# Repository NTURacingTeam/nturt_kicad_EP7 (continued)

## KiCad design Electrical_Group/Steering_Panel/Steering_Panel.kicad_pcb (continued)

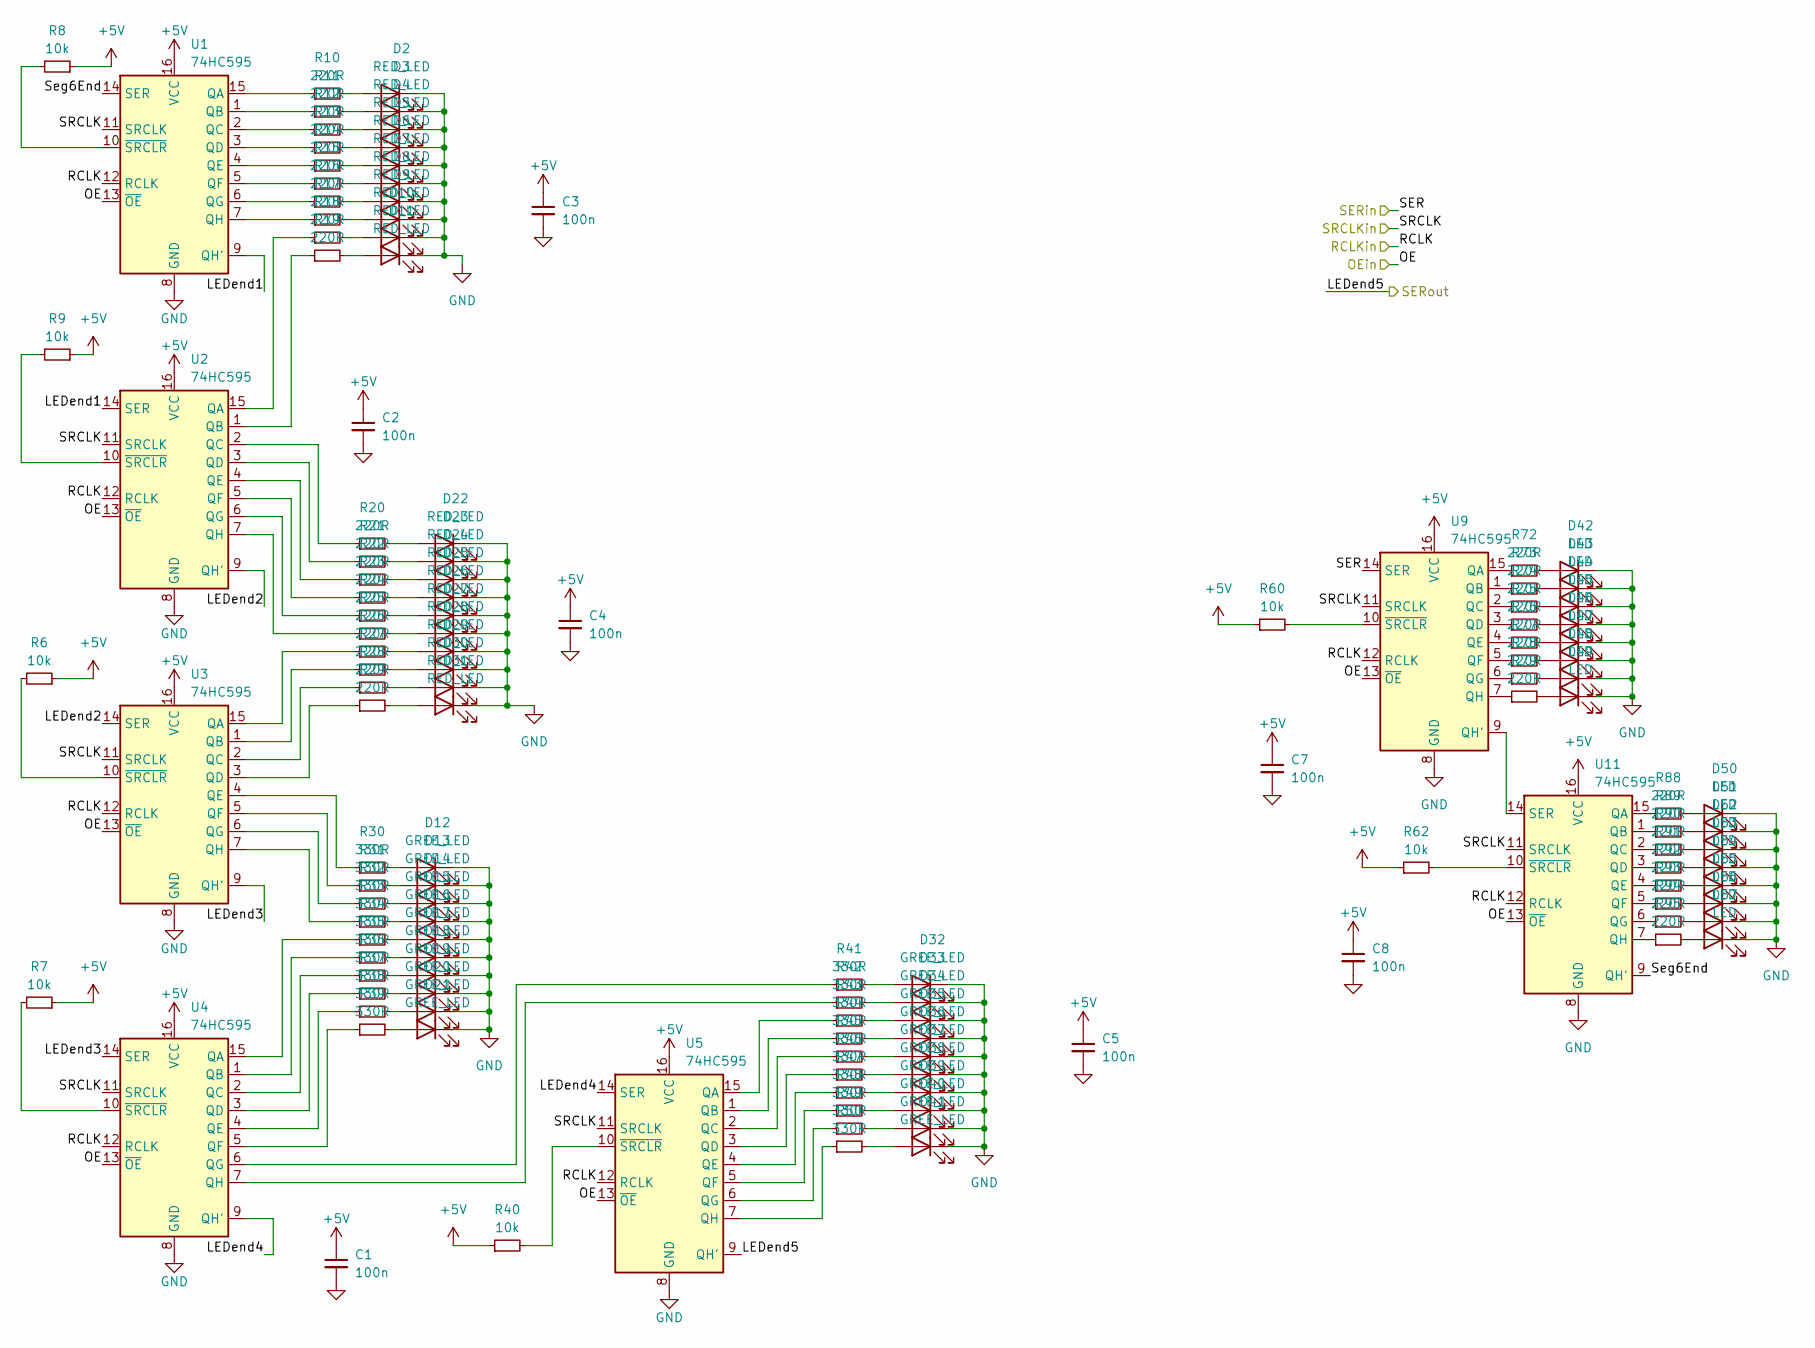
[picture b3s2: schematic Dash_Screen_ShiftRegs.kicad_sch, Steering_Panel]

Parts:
C1, C2, C3, C4, C5, C7, C8: 100n; C_0603_1608Metric
D2, D3, D4, D5, D6, D7, D8, D9, D10, D11, D22, D23, D24, D25, D26, D27, D28, D29, D30, D31: RED_LED; LED_0805_2012Metric_Pad1.15x1.40mm_HandSolder
D12, D13, D14, D15, D16, D17, D18, D19, D20, D21, D32, D33, D34, D35, D36, D37, D38, D39, D40, D41: GREE_LED; LED_0805_2012Metric_Pad1.15x1.40mm_HandSolder
D42, D43, D44, D45, D46, D47, D48, D49, D50, D51, D52, D53, D54, D55, D56, D57: LED; LED_0805_2012Metric_Pad1.15x1.40mm_HandSolder
R6, R7, R8, R9, R40, R60, R62: 10k; R_0603_1608Metric
R10, R11, R12, R13, R14, R15, R16, R17, R18, R19, R20, R21, R22, R23, R24, R25, R26, R27, R28, R29, R72, R73, R74, R75, R76, R77, R78, R79, R88, R89, R90, R91, R92, R93, R94, R95: 220R; R_0603_1608Metric_Pad0.98x0.95mm_HandSolder
R30, R31, R32, R33, R34, R35, R36, R37, R38, R39, R41, R42, R43, R44, R45, R46, R47, R48, R49, R50: 330R; R_0603_1608Metric_Pad0.98x0.95mm_HandSolder
U1, U2, U3, U4, U5, U9, U11: 74HC595; SOIC-16_3.9x9.9mm_P1.27mm

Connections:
+5V: C1.1, C2.1, C3.1, C4.1, C5.1, C7.1, C8.1, R6.1, R7.1, R8.1, R9.1, R40.1, R60.1, R62.1, U1.16 (VCC), U2.16 (VCC), U3.16 (VCC), U4.16 (VCC), U5.16 (VCC), U9.16 (VCC), U11.16 (VCC); also elsewhere on the board
/Dash_Screen_ShiftRegs/LEDend1: U1.9 (QH'), U2.14 (SER)
/Dash_Screen_ShiftRegs/LEDend2: U2.9 (QH'), U3.14 (SER)
/Dash_Screen_ShiftRegs/LEDend3: U3.9 (QH'), U4.14 (SER)
/Dash_Screen_ShiftRegs/LEDend4: U4.9 (QH'), U5.14 (SER)
/Dash_Screen_ShiftRegs/LEDend5: U5.9 (QH'); also elsewhere on the board
/Dash_Screen_ShiftRegs/OE: U1.13 (~OE), U2.13 (~OE), U3.13 (~OE), U4.13 (~OE), U5.13 (~OE), U9.13 (~OE), U11.13 (~OE); also elsewhere on the board
/Dash_Screen_ShiftRegs/RCLK: U1.12 (RCLK), U2.12 (RCLK), U3.12 (RCLK), U4.12 (RCLK), U5.12 (RCLK), U9.12 (RCLK), U11.12 (RCLK); also elsewhere on the board
/Dash_Screen_ShiftRegs/SER: U9.14 (SER); also elsewhere on the board
/Dash_Screen_ShiftRegs/SRCLK: U1.11 (SRCLK), U2.11 (SRCLK), U3.11 (SRCLK), U4.11 (SRCLK), U5.11 (SRCLK), U9.11 (SRCLK), U11.11 (SRCLK); also elsewhere on the board
/Dash_Screen_ShiftRegs/Seg6End: U1.14 (SER), U11.9 (QH')
GND: C1.2, C2.2, C3.2, C4.2, C5.2, C7.2, C8.2, D2.1 (K), D3.1 (K), D4.1 (K), D5.1 (K), D6.1 (K), D7.1 (K), D8.1 (K), D9.1 (K), D10.1 (K), D11.1 (K), D12.1 (K), D13.1 (K), D14.1 (K), D15.1 (K), D16.1 (K), D17.1 (K), D18.1 (K), D19.1 (K), D20.1 (K), D21.1 (K), D22.1 (K), D23.1 (K), D24.1 (K), D25.1 (K), D26.1 (K), D27.1 (K), D28.1 (K), D29.1 (K), D30.1 (K), D31.1 (K), D32.1 (K), D33.1 (K), D34.1 (K), D35.1 (K), D36.1 (K), D37.1 (K), D38.1 (K), D39.1 (K), D40.1 (K), D41.1 (K), D42.1 (K), D43.1 (K), D44.1 (K), D45.1 (K), D46.1 (K), D47.1 (K), D48.1 (K), D49.1 (K), D50.1 (K), D51.1 (K), D52.1 (K), D53.1 (K), D54.1 (K), D55.1 (K), D56.1 (K), D57.1 (K), U1.8 (GND), U2.8 (GND), U3.8 (GND), U4.8 (GND), U5.8 (GND), U9.8 (GND), U11.8 (GND); also elsewhere on the board
unnamed: D2.2 (A), R10.2
unnamed: D3.2 (A), R11.2
unnamed: D4.2 (A), R12.2
unnamed: D5.2 (A), R13.2
unnamed: D6.2 (A), R14.2
unnamed: D7.2 (A), R15.2
unnamed: D8.2 (A), R16.2
unnamed: D9.2 (A), R17.2
unnamed: D10.2 (A), R18.2
unnamed: D11.2 (A), R19.2
unnamed: D12.2 (A), R30.2
unnamed: D13.2 (A), R31.2
unnamed: D14.2 (A), R32.2
unnamed: D15.2 (A), R33.2
unnamed: D16.2 (A), R34.2
unnamed: D17.2 (A), R35.2
unnamed: D18.2 (A), R36.2
unnamed: D19.2 (A), R37.2
unnamed: D20.2 (A), R38.2
unnamed: D21.2 (A), R39.2
unnamed: D22.2 (A), R20.2
unnamed: D23.2 (A), R21.2
unnamed: D24.2 (A), R22.2
unnamed: D25.2 (A), R23.2
unnamed: D26.2 (A), R24.2
unnamed: D27.2 (A), R25.2
unnamed: D28.2 (A), R26.2
unnamed: D29.2 (A), R27.2
unnamed: D30.2 (A), R28.2
unnamed: D31.2 (A), R29.2
unnamed: D32.2 (A), R41.2
unnamed: D33.2 (A), R42.2
unnamed: D34.2 (A), R43.2
unnamed: D35.2 (A), R44.2
unnamed: D36.2 (A), R45.2
unnamed: D37.2 (A), R46.2
unnamed: D38.2 (A), R47.2
unnamed: D39.2 (A), R48.2
unnamed: D40.2 (A), R49.2
unnamed: D41.2 (A), R50.2
unnamed: D42.2 (A), R72.2
unnamed: D43.2 (A), R73.2
unnamed: D44.2 (A), R74.2
unnamed: D45.2 (A), R75.2
unnamed: D46.2 (A), R76.2
unnamed: D47.2 (A), R77.2
unnamed: D48.2 (A), R78.2
unnamed: D49.2 (A), R79.2
unnamed: D50.2 (A), R88.2
unnamed: D51.2 (A), R89.2
unnamed: D52.2 (A), R90.2
unnamed: D53.2 (A), R91.2
unnamed: D54.2 (A), R92.2
unnamed: D55.2 (A), R93.2
unnamed: D56.2 (A), R94.2
unnamed: D57.2 (A), R95.2
unnamed: R10.1, U1.15 (QA)
unnamed: R11.1, U1.1 (QB)
unnamed: R12.1, U1.2 (QC)
unnamed: R13.1, U1.3 (QD)
unnamed: R14.1, U1.4 (QE)
unnamed: R15.1, U1.5 (QF)
unnamed: R16.1, U1.6 (QG)
unnamed: R17.1, U1.7 (QH)
unnamed: R8.2, U1.10 (~SRCLR)
unnamed: R18.1, U2.15 (QA)
unnamed: R19.1, U2.1 (QB)
unnamed: R20.1, U2.2 (QC)
unnamed: R21.1, U2.3 (QD)
unnamed: R22.1, U2.4 (QE)
unnamed: R23.1, U2.5 (QF)
unnamed: R24.1, U2.6 (QG)
unnamed: R25.1, U2.7 (QH)
unnamed: R9.2, U2.10 (~SRCLR)
unnamed: R26.1, U3.15 (QA)
unnamed: R27.1, U3.1 (QB)
unnamed: R28.1, U3.2 (QC)
unnamed: R29.1, U3.3 (QD)
unnamed: R30.1, U3.4 (QE)
unnamed: R31.1, U3.5 (QF)
unnamed: R32.1, U3.6 (QG)
unnamed: R33.1, U3.7 (QH)
unnamed: R6.2, U3.10 (~SRCLR)
unnamed: R34.1, U4.15 (QA)
unnamed: R35.1, U4.1 (QB)
unnamed: R36.1, U4.2 (QC)
unnamed: R37.1, U4.3 (QD)
unnamed: R38.1, U4.4 (QE)
unnamed: R39.1, U4.5 (QF)
unnamed: R41.1, U4.6 (QG)
unnamed: R42.1, U4.7 (QH)
unnamed: R7.2, U4.10 (~SRCLR)
unnamed: R43.1, U5.15 (QA)
unnamed: R44.1, U5.1 (QB)
unnamed: R45.1, U5.2 (QC)
unnamed: R46.1, U5.3 (QD)
unnamed: R47.1, U5.4 (QE)
unnamed: R48.1, U5.5 (QF)
unnamed: R49.1, U5.6 (QG)
unnamed: R50.1, U5.7 (QH)
unnamed: R40.2, U5.10 (~SRCLR)
unnamed: R72.1, U9.15 (QA)
unnamed: R73.1, U9.1 (QB)
unnamed: R74.1, U9.2 (QC)
unnamed: R75.1, U9.3 (QD)
unnamed: R76.1, U9.4 (QE)
unnamed: R77.1, U9.5 (QF)
unnamed: R78.1, U9.6 (QG)
unnamed: R79.1, U9.7 (QH)
unnamed: R60.2, U9.10 (~SRCLR)
unnamed: R88.1, U11.15 (QA)
unnamed: R89.1, U11.1 (QB)
unnamed: R90.1, U11.2 (QC)
unnamed: R91.1, U11.3 (QD)
unnamed: R92.1, U11.4 (QE)
unnamed: R93.1, U11.5 (QF)
unnamed: R94.1, U11.6 (QG)
unnamed: R95.1, U11.7 (QH)
unnamed: U9.9 (QH'), U11.14 (SER)
unnamed: R62.2, U11.10 (~SRCLR)

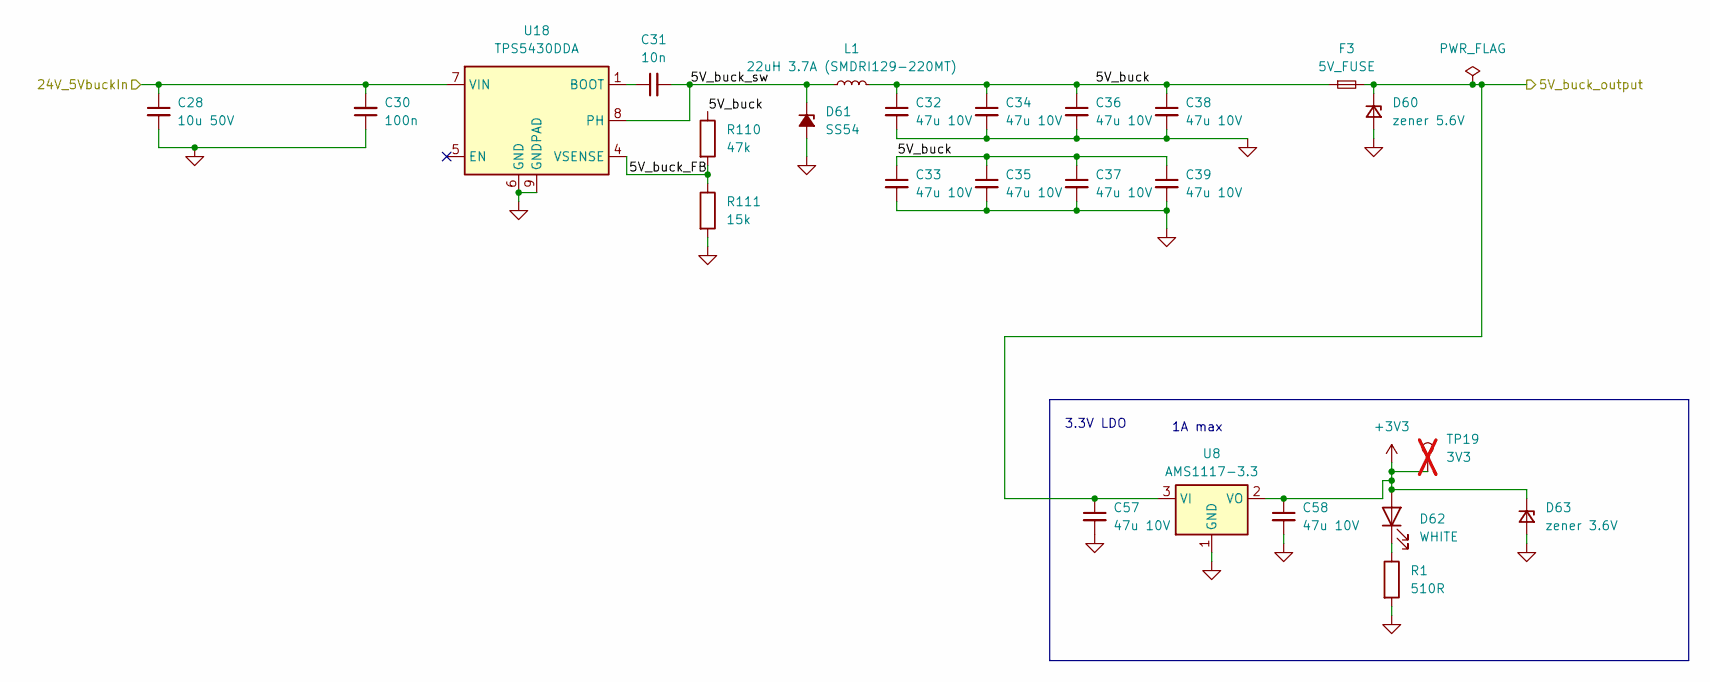
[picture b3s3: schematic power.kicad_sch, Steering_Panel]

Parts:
C28: 10u 50V; C_1206_3216Metric
C30: 100n; C_0603_1608Metric
C31: 10n; C_0603_1608Metric
C32, C33, C34, C35, C36, C37, C38, C39, C57, C58: 47u 10V; C_1206_3216Metric
D60: zener 5.6V; D_SOD-123
D61: SS54; D_SMA
D62: WHITE; LED_0603_1608Metric
D63: zener 3.6V; D_SOD-123
F3: 5V_FUSE; Fuse_1206_3216Metric
L1: 22uH 3.7A (SMDRI129-220MT); L_Bourns_SRR1260
R1: 510R; R_0603_1608Metric
R110: 47k; R_0603_1608Metric
R111: 15k; R_0603_1608Metric
TP19: 3V3; TestPoint_Pad_D1.0mm; not fitted
U8: AMS1117-3.3; SOT-223-3_TabPin2
U18: TPS5430DDA; TI_SO-PowerPAD-8

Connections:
+3V3: C58.1, D62.2 (A), D63.1 (K), TP19.1, U8.2 (VO); also elsewhere on the board
+5V: C57.1, D60.1 (K), F3.2, U8.3 (VI); also elsewhere on the board
/power/5V_buck: C32.1, C33.1, C34.1, C35.1, C36.1, C37.1, C38.1, C39.1, F3.1, L1.2, R110.1
/power/5V_buck_FB: R110.2, R111.1, U18.4 (VSENSE)
/power/5V_buck_sw: C31.2, D61.1 (K), L1.1, U18.8 (PH)
/power/24V_5VbuckIn: C28.1, C30.2, U18.7 (VIN); also elsewhere on the board
GND: C28.2, C30.1, C32.2, C33.2, C34.2, C35.2, C36.2, C37.2, C38.2, C39.2, C57.2, C58.2, D60.2 (A), D61.2 (A), D63.2 (A), R1.2, R111.2, U8.1 (GND), U18.6 (GND), U18.9 (GNDPAD); also elsewhere on the board
unnamed: D62.1 (K), R1.1
unnamed: C31.1, U18.1 (BOOT)

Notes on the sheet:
1A max
3.3V LDO

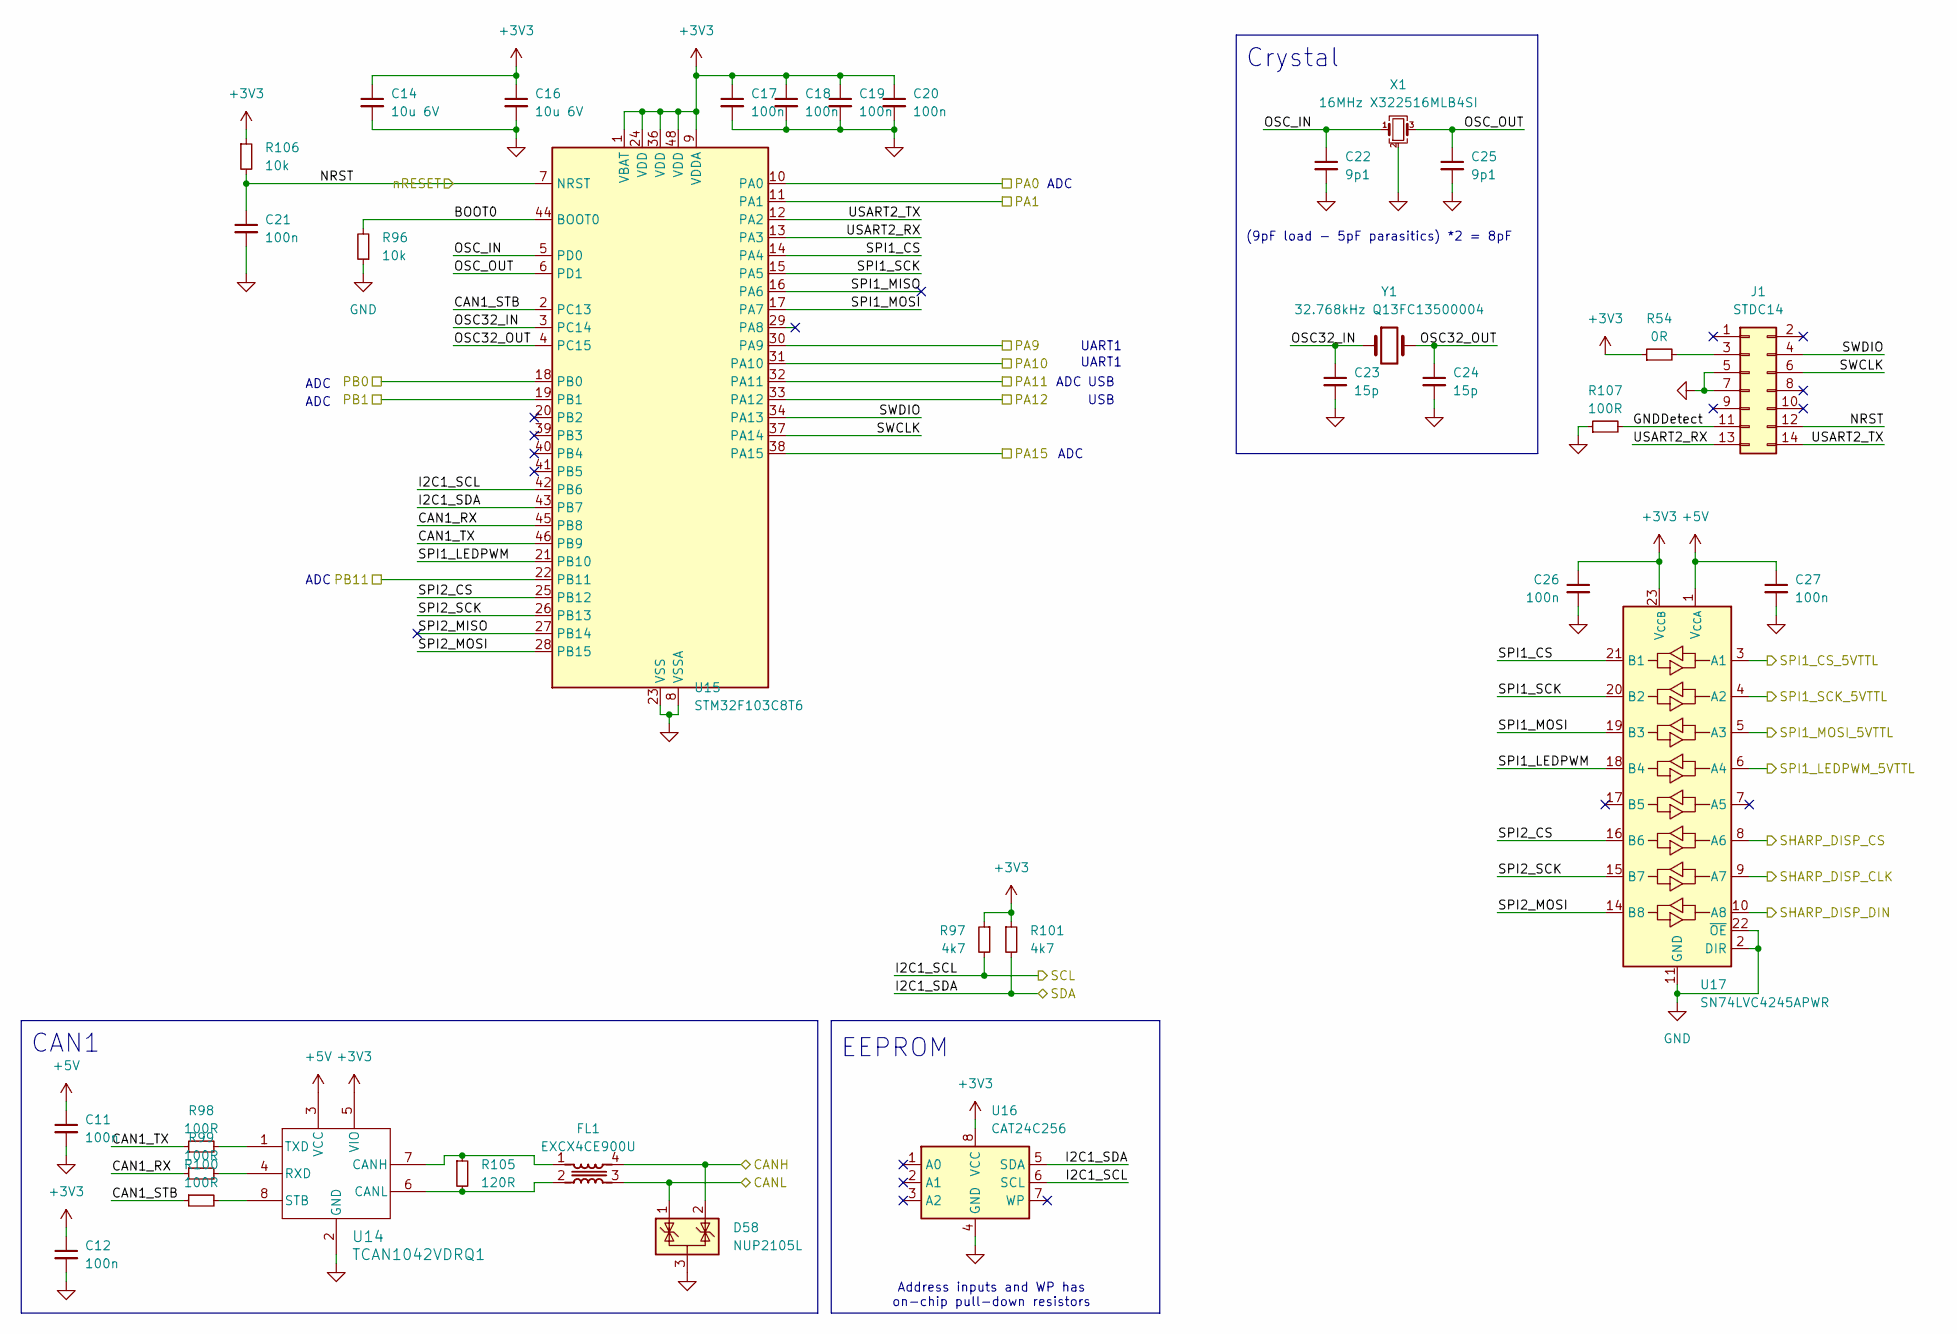
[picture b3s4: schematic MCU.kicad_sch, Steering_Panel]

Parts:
C11, C12, C17, C18, C19, C20, C21, C26, C27: 100n; C_0603_1608Metric
C14, C16: 10u 6V; C_0603_1608Metric
C22, C25: 9p1; C_0603_1608Metric
C23, C24: 15p; C_0603_1608Metric
D58: NUP2105L; SOT-23
FL1: EXCX4CE900U; Mouser Part Number 667-EXC-X4CE900U
J1: STDC14; box_header_14P_pitch1.27_smd
R54: 0R; R_0603_1608Metric
R96, R106: 10k; R_0603_1608Metric
R97, R101: 4k7; R_0603_1608Metric
R98, R99, R100, R107: 100R; R_0603_1608Metric
R105: 120R; R_0603_1608Metric
U14: TCAN1042VDRQ1; SOIC-8_3.9x4.9mm_P1.27mm
U15: STM32F103C8T6; LQFP-48_7x7mm_P0.5mm
U16: CAT24C256; SOIC-8_3.9x4.9mm_P1.27mm
U17: SN74LVC4245APWR; TSSOP-24_4.4x7.8mm_P0.65mm
X1: 16MHz X322516MLB4SI; Crystal_SMD_3225-4Pin_3.2x2.5mm
Y1: 32.768kHz Q13FC13500004; Crystal_SMD_3215-2Pin_3.2x1.5mm

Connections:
+3V3: C12.1, C14.1, C16.1, C17.1, C18.1, C19.1, C20.1, C26.1, R54.1, R97.1, R101.1, R106.1, U14.5 (VIO), U15.1 (VBAT), U15.9 (VDDA), U15.24 (VDD), U15.36 (VDD), U15.48 (VDD), U16.8 (VCC), U17.23 (V_{CCB}), U17.24 (V_{CCB}); also elsewhere on the board
+5V: C11.1, C27.1, U14.3 (VCC), U17.1 (V_{CCA}); also elsewhere on the board
/DISP_CLK: U17.9 (A7); also elsewhere on the board
/DISP_CS: U17.8 (A6); also elsewhere on the board
/DISP_DIN: U17.10 (A8); also elsewhere on the board
/Dash_Screen_ShiftRegs/OE: U17.6 (A4); also elsewhere on the board
/Dash_Screen_ShiftRegs/RCLK: U17.3 (A1); also elsewhere on the board
/Dash_Screen_ShiftRegs/SER: U17.5 (A3); also elsewhere on the board
/Dash_Screen_ShiftRegs/SRCLK: U17.4 (A2); also elsewhere on the board
/I2C_SCL: R97.2, U15.42 (PB6), U16.6 (SCL); also elsewhere on the board
/I2C_SDA: R101.2, U15.43 (PB7), U16.5 (SDA); also elsewhere on the board
/MCU/BOOT0: R96.2, U15.44 (BOOT0)
/MCU/CAN1_RX: R99.1, U15.45 (PB8)
/MCU/CAN1_STB: R100.1, U15.2 (PC13)
/MCU/CAN1_TX: R98.1, U15.46 (PB9)
/MCU/CANH: D58.2 (K), FL1.4; also elsewhere on the board
/MCU/CANL: D58.1 (K), FL1.3; also elsewhere on the board
/MCU/GNDDetect: J1.11, R107.2
/MCU/NRST: C21.1, J1.12, R106.2, U15.7 (NRST); also elsewhere on the board
/MCU/OSC32_IN: C23.1, U15.3 (PC14), Y1.1
/MCU/OSC32_OUT: C24.1, U15.4 (PC15), Y1.2
/MCU/OSC_IN: C22.1, U15.5 (PD0), X1.1
/MCU/OSC_OUT: C25.1, U15.6 (PD1), X1.3
/MCU/PA0: U15.10 (PA0); also elsewhere on the board
/MCU/PA1: U15.11 (PA1); also elsewhere on the board
/MCU/PA9: U15.30 (PA9); also elsewhere on the board
/MCU/PA10: U15.31 (PA10); also elsewhere on the board
/MCU/PA11: U15.32 (PA11); also elsewhere on the board
/MCU/PA12: U15.33 (PA12); also elsewhere on the board
/MCU/PA15: U15.38 (PA15); also elsewhere on the board
/MCU/PB0: U15.18 (PB0); also elsewhere on the board
/MCU/PB1: U15.19 (PB1); also elsewhere on the board
/MCU/PB11: U15.22 (PB11); also elsewhere on the board
/MCU/SPI1_CS: U15.14 (PA4), U17.21 (B1)
/MCU/SPI1_LEDPWM: U15.21 (PB10), U17.18 (B4)
/MCU/SPI1_MISO: U15.16 (PA6)
/MCU/SPI1_MOSI: U15.17 (PA7), U17.19 (B3)
/MCU/SPI1_SCK: U15.15 (PA5), U17.20 (B2)
/MCU/SPI2_CS: U15.25 (PB12), U17.16 (B6)
/MCU/SPI2_MISO: U15.27 (PB14)
/MCU/SPI2_MOSI: U15.28 (PB15), U17.14 (B8)
/MCU/SPI2_SCK: U15.26 (PB13), U17.15 (B7)
/MCU/SWCLK: J1.6, U15.37 (PA14)
/MCU/SWDIO: J1.4, U15.34 (PA13)
/MCU/USART2_RX: J1.13, U15.13 (PA3)
/MCU/USART2_TX: J1.14, U15.12 (PA2)
GND: C11.2, C12.2, C14.2, C16.2, C17.2, C18.2, C19.2, C20.2, C21.2, C22.2, C23.2, C24.2, C25.2, C26.2, C27.2, D58.3 (A), J1.5, J1.7, R96.1, R107.1, U14.2 (GND), U15.8 (VSSA), U15.23 (VSS), U15.35 (VSS), U15.47 (VSS), U16.4 (GND), U17.2 (DIR), U17.11 (GND), U17.12 (GND), U17.13 (GND), U17.22 (~OE), X1.2 (G), X1.4 (G); also elsewhere on the board
unnamed: J1.3, R54.2
unnamed: FL1.1, R105.1, U14.7 (CANH)
unnamed: FL1.2, R105.2, U14.6 (CANL)
unnamed: R99.2, U14.4 (RXD)
unnamed: R100.2, U14.8 (STB)
unnamed: R98.2, U14.1 (TXD)

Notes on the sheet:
USB
ADC
Address inputs and WP has on-chip pull-down resistors
CAN1
(9pF load - 5pF parasitics) *2 = 8pF
UART1
Crystal
EEPROM

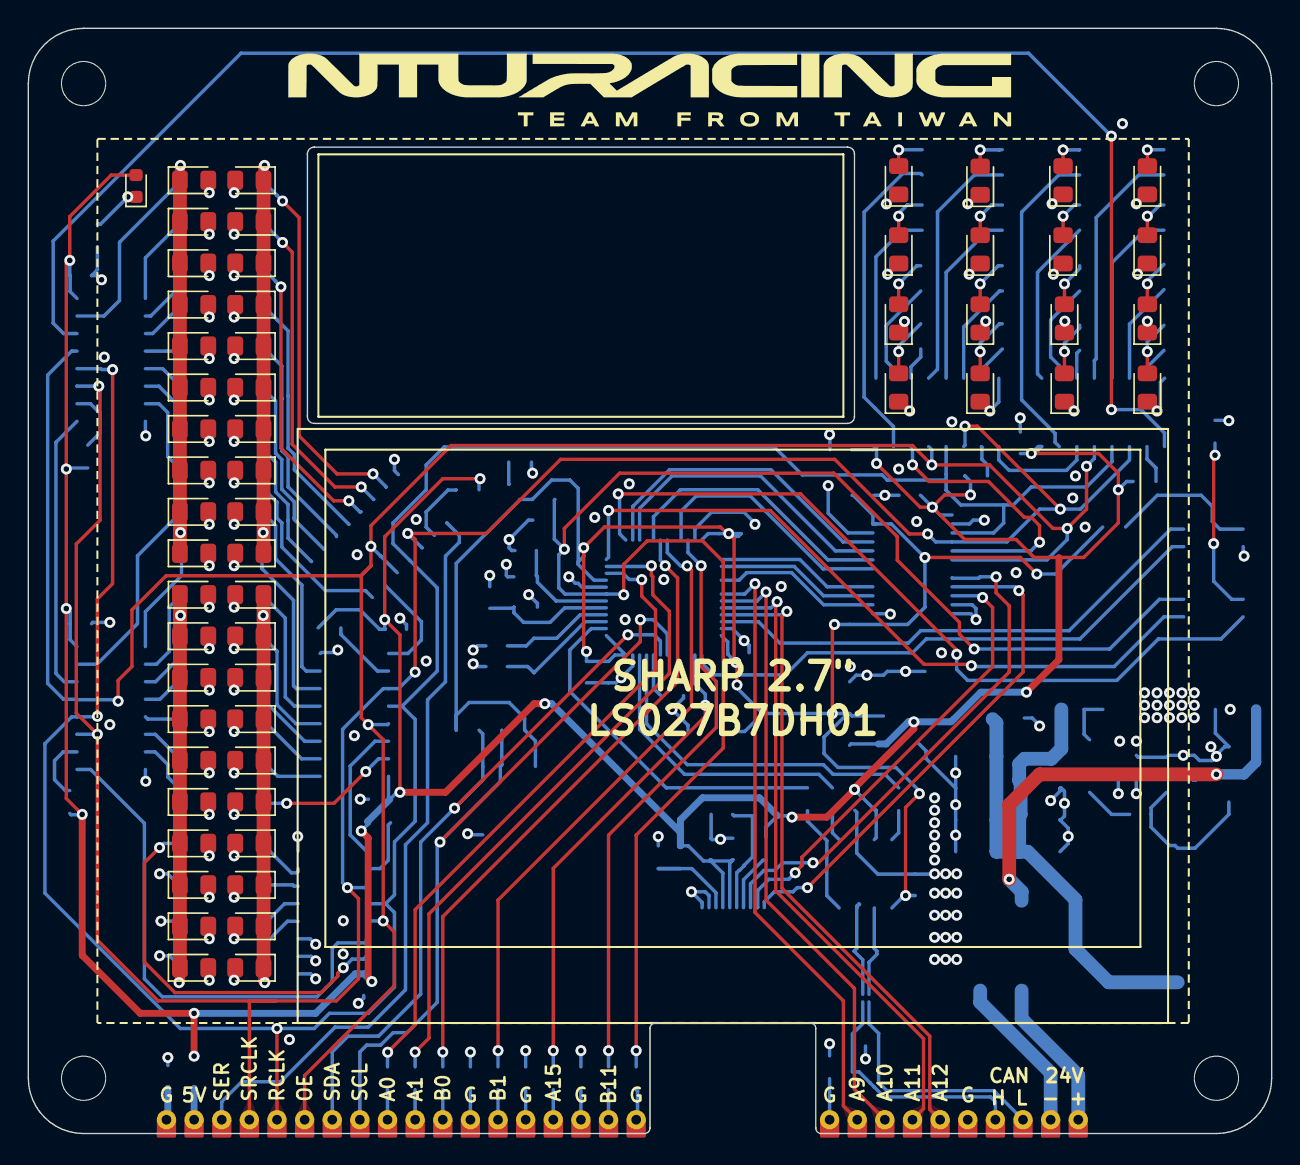
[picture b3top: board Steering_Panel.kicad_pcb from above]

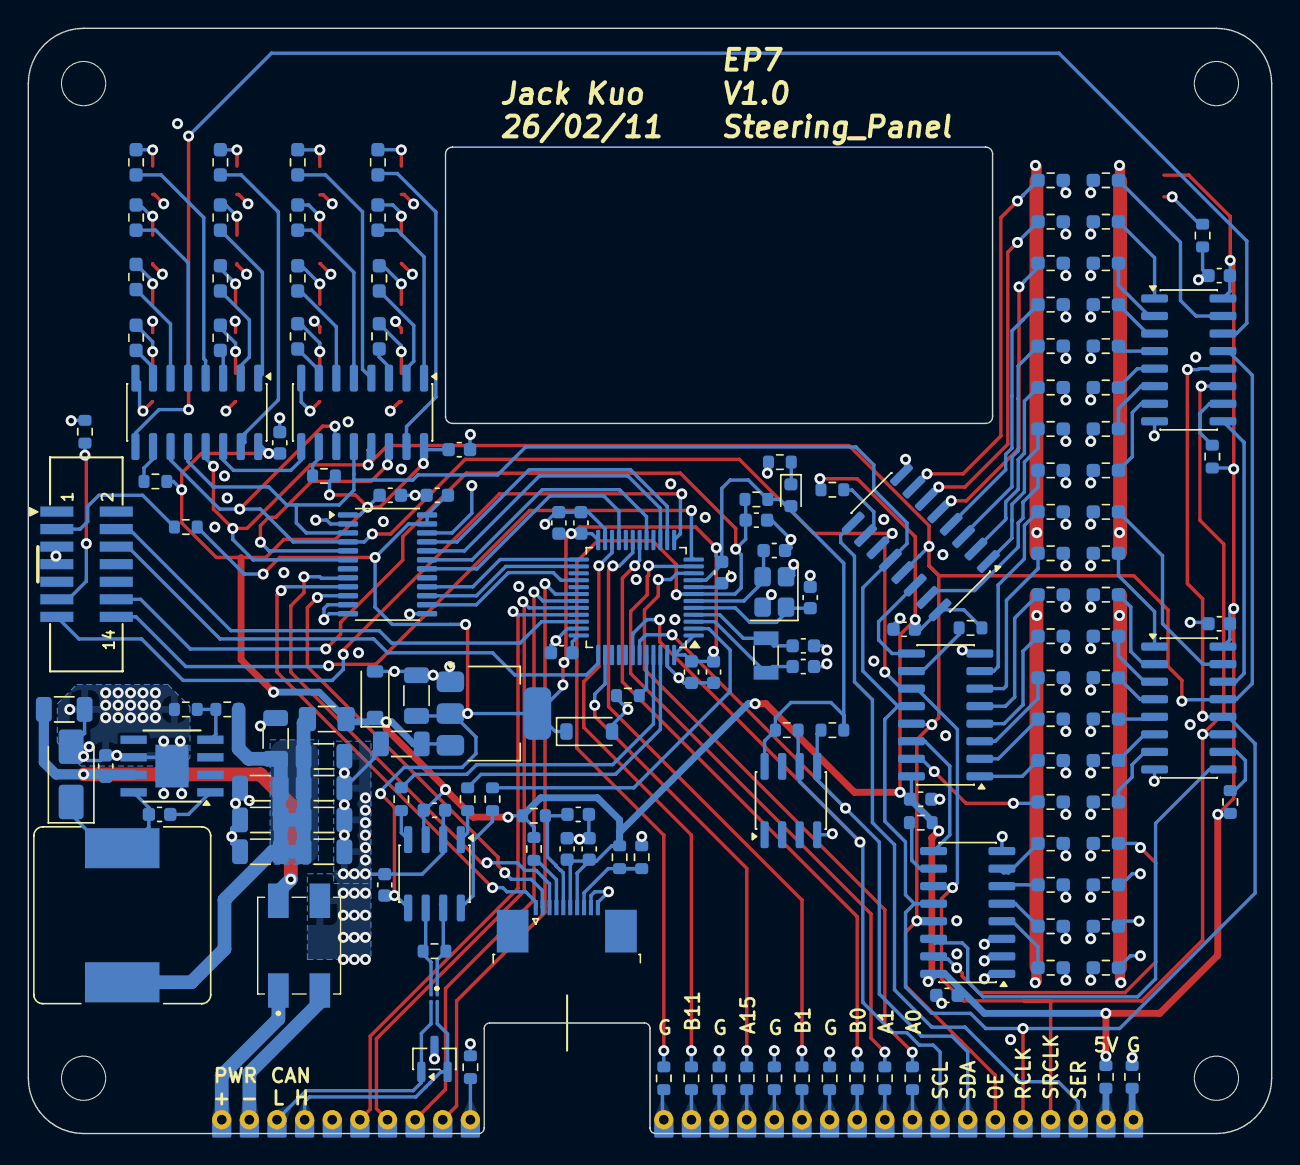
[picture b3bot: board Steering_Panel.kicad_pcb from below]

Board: 4 copper layers, 90.0 x 80.0 mm, 247 parts (162 on the bottom side), 202 nets.

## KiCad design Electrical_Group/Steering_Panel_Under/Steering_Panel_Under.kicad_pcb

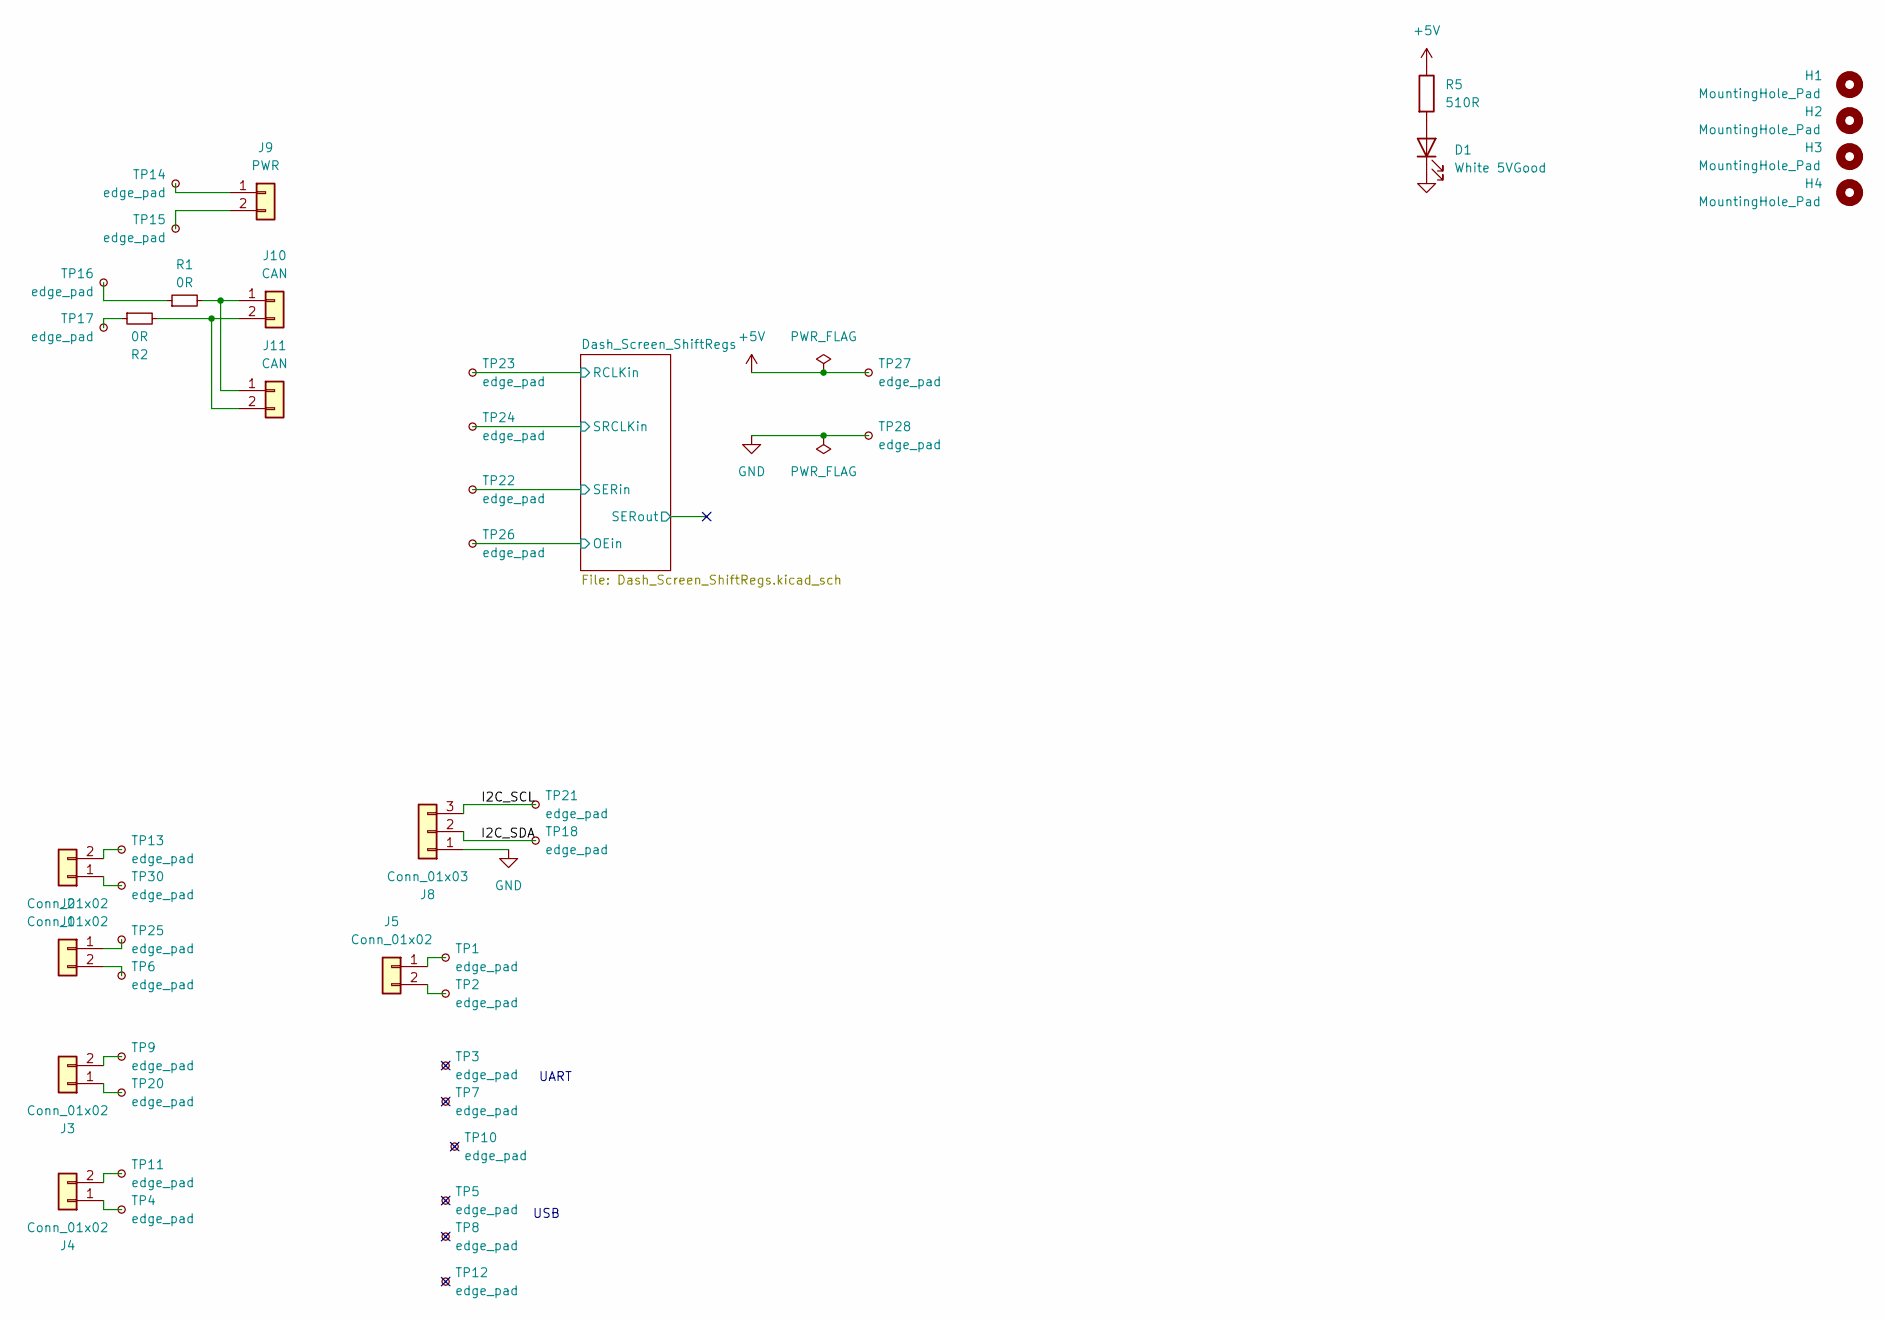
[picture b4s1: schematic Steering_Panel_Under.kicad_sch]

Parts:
D1: White 5VGood; LED_0603_1608Metric
H1, H2, H3, H4: MountingHole_Pad; MountingHole_3.2mm_M3
J1, J2, J3, J4, J5: Conn_01x02; JST_PH_S2B-PH-K_1x02_P2.00mm_Horizontal
J8: Conn_01x03; JST_PH_S3B-PH-K_1x03_P2.00mm_Horizontal
J9: PWR; JST_XH_S2B-XH-A_1x02_P2.50mm_Horizontal
J10, J11: CAN; JST_XH_S2B-XH-A_1x02_P2.50mm_Horizontal
R1, R2: 0R; R_0603_1608Metric
R5: 510R; R_0603_1608Metric
TP1, TP2, TP3, TP4, TP5, TP6, TP7, TP8, TP9, TP10, TP11, TP12, TP13, TP14, TP15, TP16, TP17, TP18, TP20, TP21, TP22, TP23, TP24, TP25, TP26, TP27, TP28, TP30: edge_pad; edge_pad_1.4mm_0.7mm

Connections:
+5V: R5.1, TP27.1; also elsewhere on the board
/Dash_Screen_ShiftRegs/OE: TP26.1; also elsewhere on the board
/Dash_Screen_ShiftRegs/RCLK: TP23.1; also elsewhere on the board
/Dash_Screen_ShiftRegs/SER: TP22.1; also elsewhere on the board
/Dash_Screen_ShiftRegs/SRCLK: TP24.1; also elsewhere on the board
/I2C_SCL: J8.3, TP21.1
/I2C_SDA: J8.2, TP18.1
GND: D1.1 (K), J8.1, TP28.1; also elsewhere on the board
unnamed: D1.2 (A), R5.2
unnamed: J1.1, TP30.1
unnamed: J1.2, TP13.1
unnamed: J2.1, TP25.1
unnamed: J2.2, TP6.1
unnamed: J3.1, TP20.1
unnamed: J3.2, TP9.1
unnamed: J4.1, TP4.1
unnamed: J4.2, TP11.1
unnamed: J5.1, TP1.1
unnamed: J5.2, TP2.1
unnamed: J9.1, TP14.1
unnamed: J9.2, TP15.1
unnamed: J10.1, J11.1, R1.2
unnamed: J10.2, J11.2, R2.2
unnamed: R1.1, TP16.1
unnamed: R2.1, TP17.1

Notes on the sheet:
UART
USB

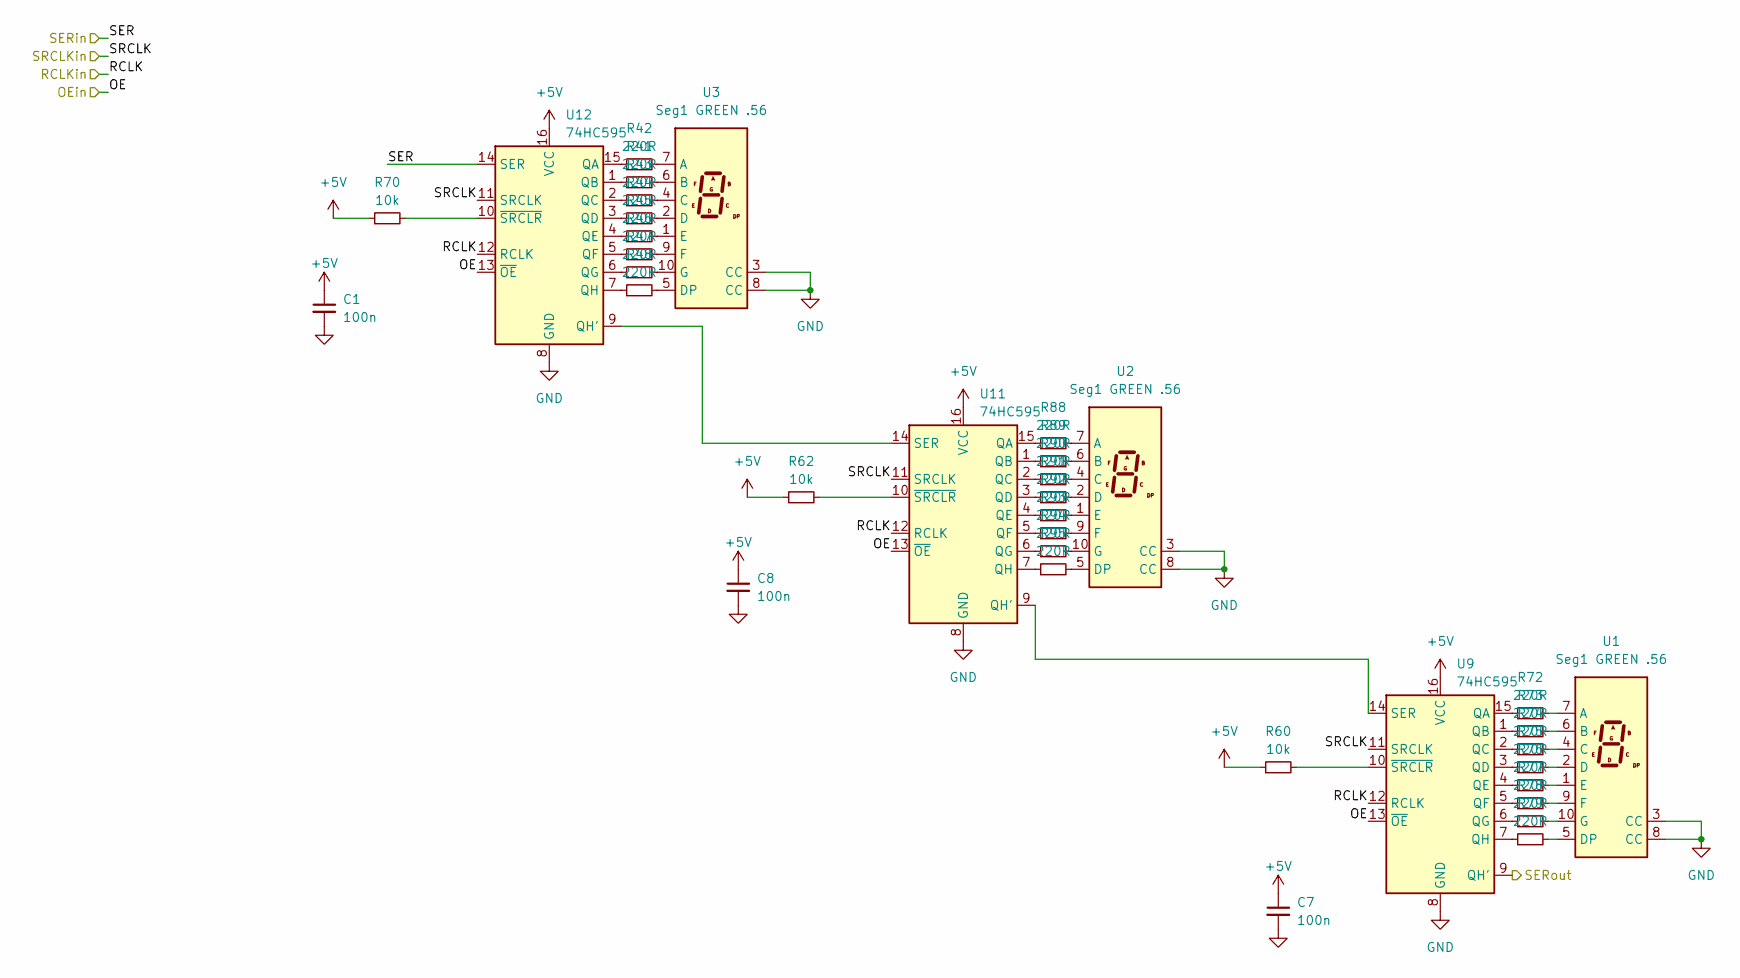
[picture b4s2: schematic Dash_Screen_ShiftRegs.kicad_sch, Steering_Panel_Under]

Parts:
C1, C7, C8: 100n; C_0603_1608Metric
R41, R42, R43, R44, R45, R46, R47, R48, R72, R73, R74, R75, R76, R77, R78, R79, R88, R89, R90, R91, R92, R93, R94, R95: 220R; R_0603_1608Metric_Pad0.98x0.95mm_HandSolder
R60, R62, R70: 10k; R_0603_1608Metric
U1, U2, U3: Seg1 GREEN .56; 7SegmentLED_LTS6760_LTS6780
U9, U11, U12: 74HC595; SOIC-16_3.9x9.9mm_P1.27mm

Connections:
+5V: C1.1, C7.1, C8.1, R60.1, R62.1, R70.1, U9.16 (VCC), U11.16 (VCC), U12.16 (VCC); also elsewhere on the board
/Dash_Screen_ShiftRegs/OE: U9.13 (~OE), U11.13 (~OE), U12.13 (~OE); also elsewhere on the board
/Dash_Screen_ShiftRegs/RCLK: U9.12 (RCLK), U11.12 (RCLK), U12.12 (RCLK); also elsewhere on the board
/Dash_Screen_ShiftRegs/SER: U12.14 (SER); also elsewhere on the board
/Dash_Screen_ShiftRegs/SERout: U9.9 (QH')
/Dash_Screen_ShiftRegs/SRCLK: U9.11 (SRCLK), U11.11 (SRCLK), U12.11 (SRCLK); also elsewhere on the board
GND: C1.2, C7.2, C8.2, U1.3 (CC), U1.8 (CC), U2.3 (CC), U2.8 (CC), U3.3 (CC), U3.8 (CC), U9.8 (GND), U11.8 (GND), U12.8 (GND); also elsewhere on the board
unnamed: R72.2, U1.7 (A)
unnamed: R73.2, U1.6 (B)
unnamed: R74.2, U1.4 (C)
unnamed: R75.2, U1.2 (D)
unnamed: R79.2, U1.5 (DP)
unnamed: R76.2, U1.1 (E)
unnamed: R77.2, U1.9 (F)
unnamed: R78.2, U1.10 (G)
unnamed: R88.2, U2.7 (A)
unnamed: R89.2, U2.6 (B)
unnamed: R90.2, U2.4 (C)
unnamed: R91.2, U2.2 (D)
unnamed: R95.2, U2.5 (DP)
unnamed: R92.2, U2.1 (E)
unnamed: R93.2, U2.9 (F)
unnamed: R94.2, U2.10 (G)
unnamed: R42.2, U3.7 (A)
unnamed: R41.2, U3.6 (B)
unnamed: R43.2, U3.4 (C)
unnamed: R44.2, U3.2 (D)
unnamed: R48.2, U3.5 (DP)
unnamed: R45.2, U3.1 (E)
unnamed: R46.2, U3.9 (F)
unnamed: R47.2, U3.10 (G)
unnamed: R72.1, U9.15 (QA)
unnamed: R73.1, U9.1 (QB)
unnamed: R74.1, U9.2 (QC)
unnamed: R75.1, U9.3 (QD)
unnamed: R76.1, U9.4 (QE)
unnamed: R77.1, U9.5 (QF)
unnamed: R78.1, U9.6 (QG)
unnamed: R79.1, U9.7 (QH)
unnamed: R60.2, U9.10 (~SRCLR)
unnamed: R88.1, U11.15 (QA)
unnamed: R89.1, U11.1 (QB)
unnamed: R90.1, U11.2 (QC)
unnamed: R91.1, U11.3 (QD)
unnamed: R92.1, U11.4 (QE)
unnamed: R93.1, U11.5 (QF)
unnamed: R94.1, U11.6 (QG)
unnamed: U9.14 (SER), U11.9 (QH')
unnamed: R95.1, U11.7 (QH)
unnamed: U11.14 (SER), U12.9 (QH')
unnamed: R62.2, U11.10 (~SRCLR)
unnamed: R42.1, U12.15 (QA)
unnamed: R41.1, U12.1 (QB)
unnamed: R43.1, U12.2 (QC)
unnamed: R44.1, U12.3 (QD)
unnamed: R45.1, U12.4 (QE)
unnamed: R46.1, U12.5 (QF)
unnamed: R47.1, U12.6 (QG)
unnamed: R48.1, U12.7 (QH)
unnamed: R70.2, U12.10 (~SRCLR)
